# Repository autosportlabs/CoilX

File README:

DESCRIPTION:

CoilInterface is a compact opto-isolated interface board designed to adapt the HV kickback pulse
from an automotive coil pack primary to a digital signal that can be safely consumed by
a 0-5v digital input.

The board is sized to be shrink-wrapped and installed inline to a wiring harness.
 
LICENSE:

The technical artifacts provided in this project is covered in a modified version of the
Creative Commons BY-SA license - see the LICENESE file for the full text.

MORE INFO:

for more information visit http://www.autosportlabs.net

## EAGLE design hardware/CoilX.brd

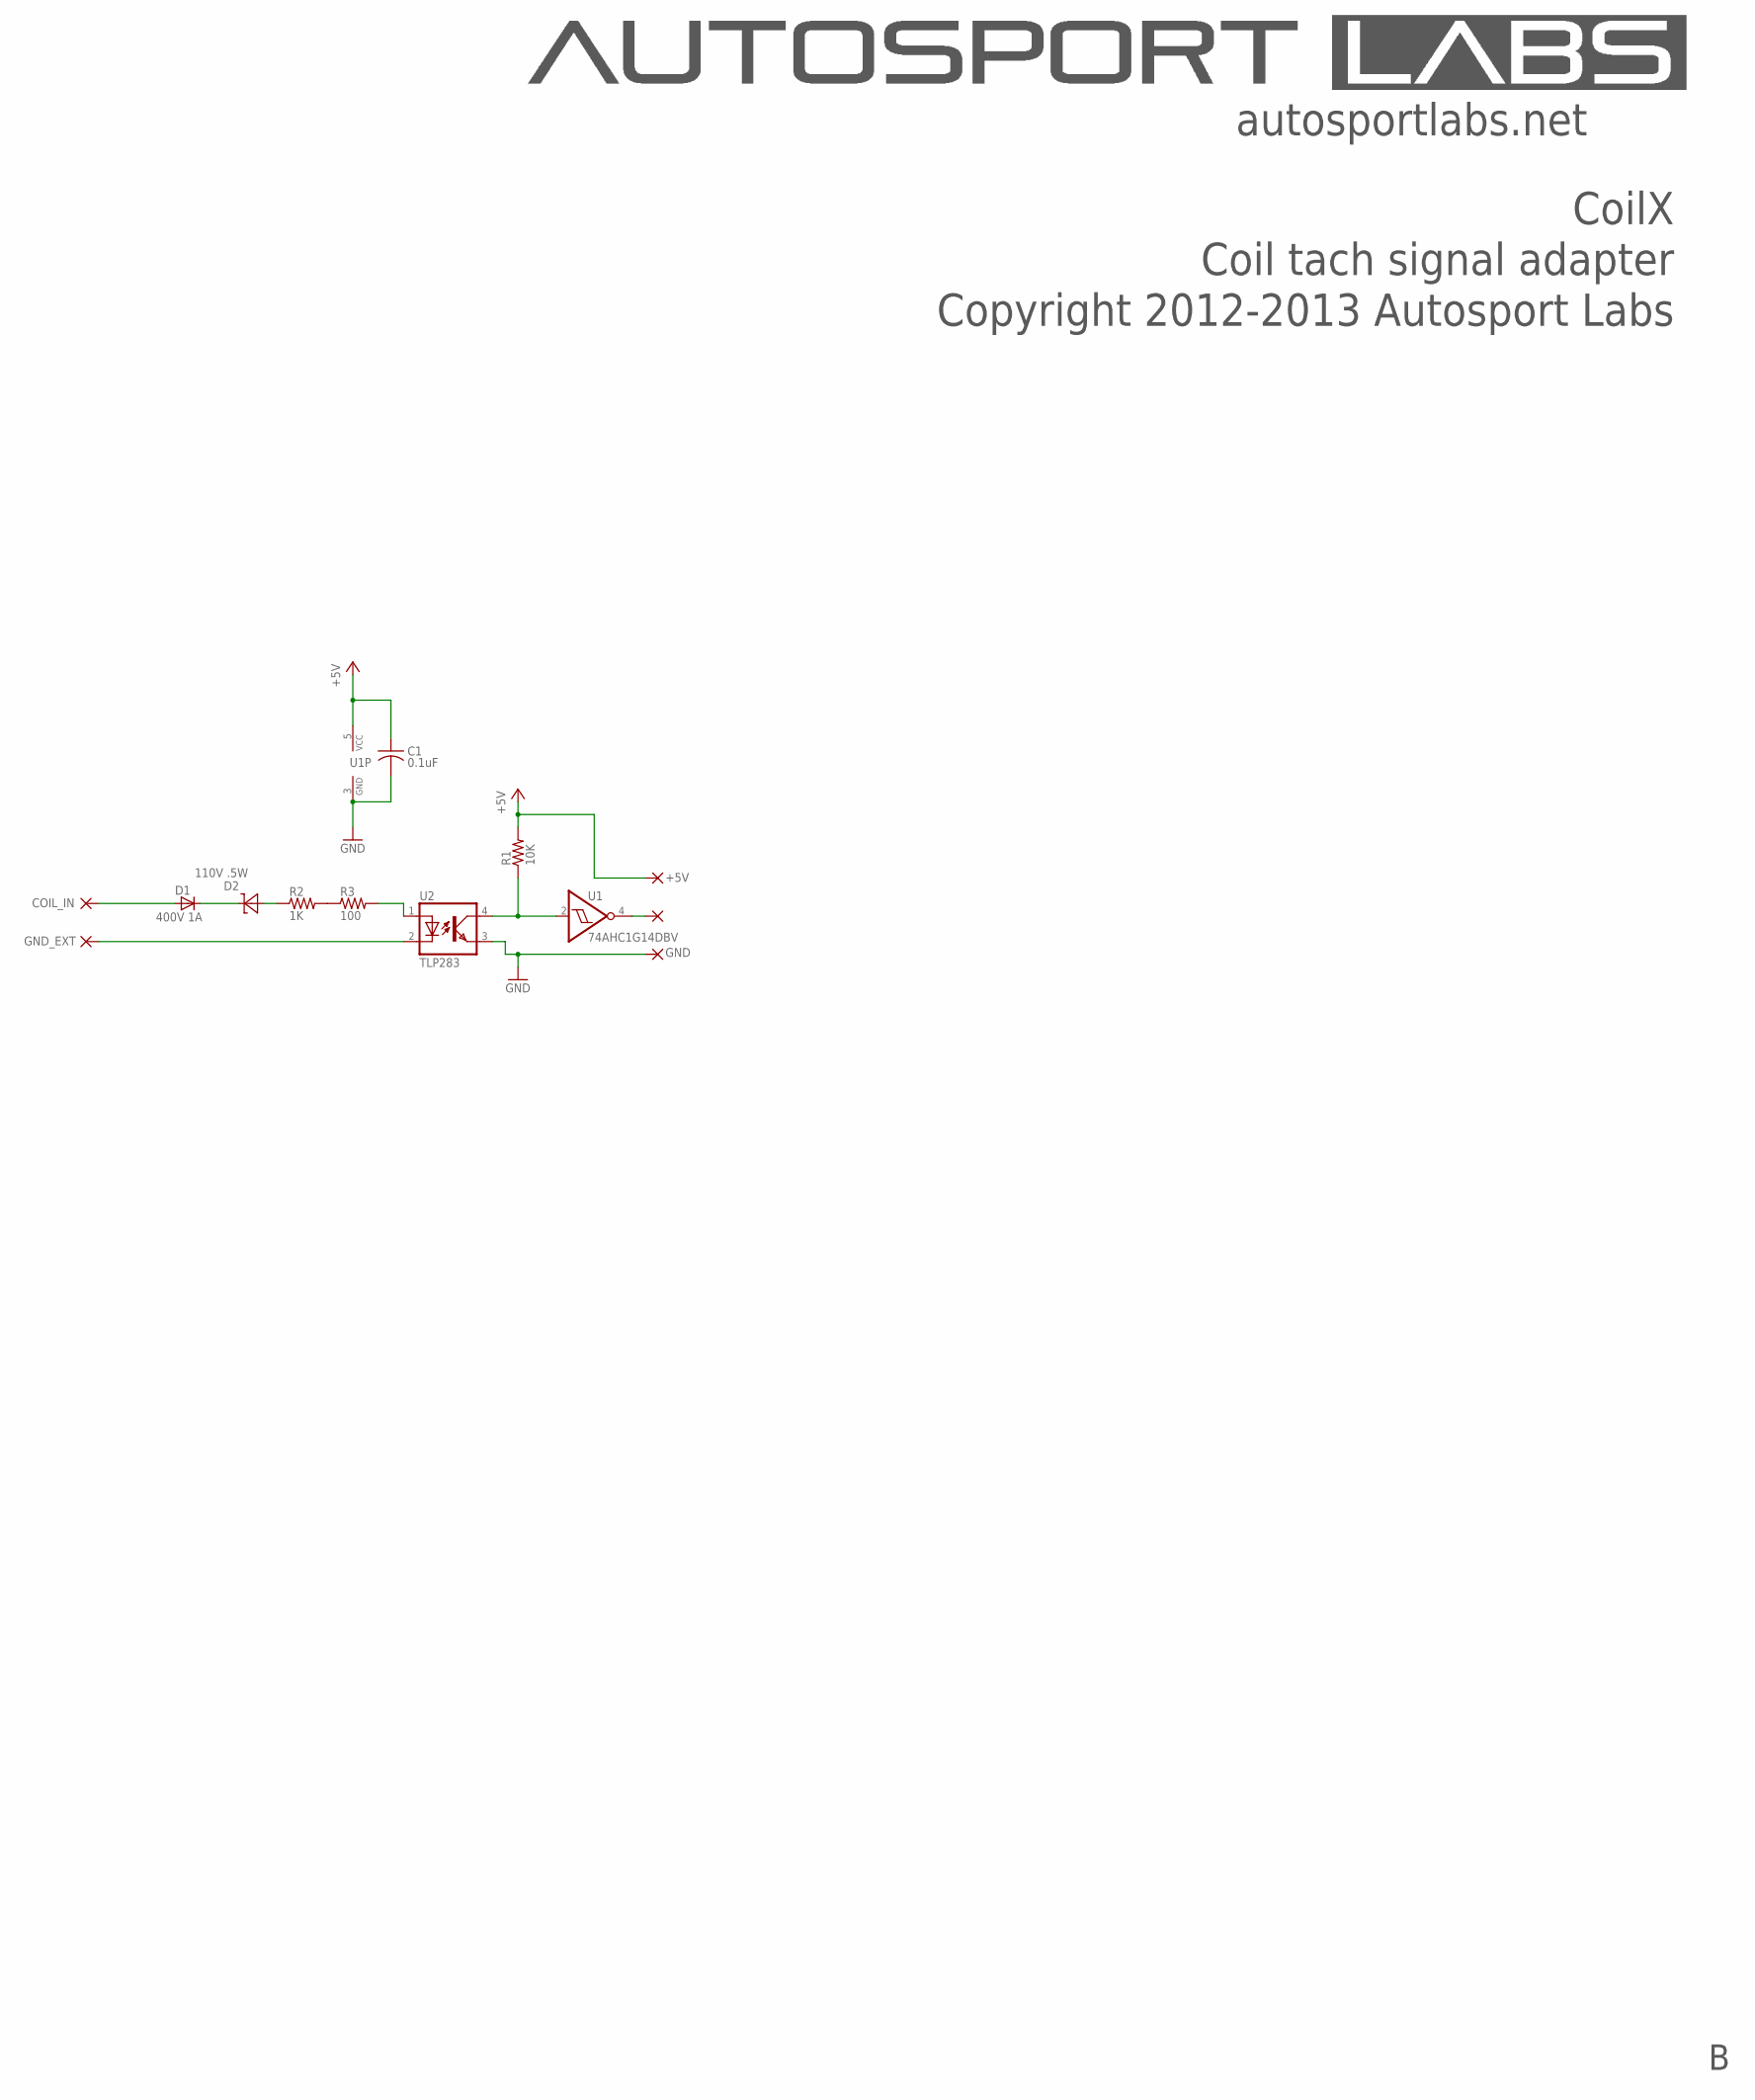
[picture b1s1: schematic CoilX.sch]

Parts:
+5V: WIREPAD3,17/1,2; 3,17/1,2
C1: 0.1uF; C0603
COIL: WIREPAD3,17/1,2; 3,17/1,2
D1: 400V 1A; SMA
D2: 110V .5W; SOD123
GND: WIREPAD3,17/1,2; 3,17/1,2
GND_EXT: WIREPAD3,17/1,2; 3,17/1,2
OUT: WIREPAD3,17/1,2; 3,17/1,2
R1: 10K; R0603
R2: 1K; R1206
R3: 100; R0603
U1: 74AHC1G14DBV; SOT23-5
U2: TLP283; MINI-FLAT-4

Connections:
+5V: +5V.1, C1.1, R1.2, U1.5 (VCC)
COIL_IN: COIL.1, D1.A
FREQ_1_IN_LOGIC: R2.2, R3.1
GND: C1.2, GND.1, U1.3 (GND), U2.3 (EMIT)
GND_EXT: GND_EXT.1, U2.2 (C)
unnamed: D2.A, R2.1
unnamed: OUT.1, U1.4 (O)
unnamed: R3.2, U2.1 (A)
unnamed: D1.C, D2.C
OPTO_TACH_OUT: R1.1, U1.2 (I), U2.4 (COL)

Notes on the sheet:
Copyright 2012-2013 Autosport Labs
CoilX
autosportlabs.net
Coil tach signal adapter

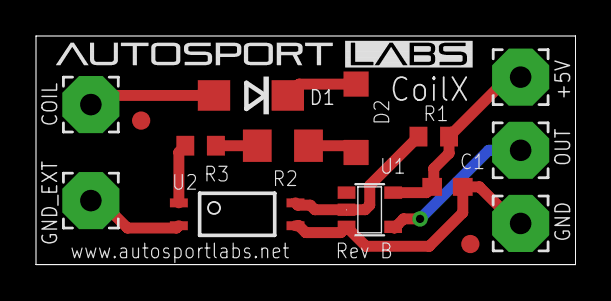
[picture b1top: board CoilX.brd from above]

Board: 2 copper layers, 30.0 x 12.7 mm, 13 parts (0 on the bottom side), 10 nets.

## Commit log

2012-04-08 added design files for CoilX
2013-04-22 updates for rev B
2013-04-22 removed secondary screenshot
2013-04-22 changed Readme to markdown
2013-04-22 removed 2nd screenshot again
2013-09-17 changed fiducials
2013-10-07 changed zener diode to 75v
2015-09-27 updated zener to 110v
2021-12-05 Create CoilX
